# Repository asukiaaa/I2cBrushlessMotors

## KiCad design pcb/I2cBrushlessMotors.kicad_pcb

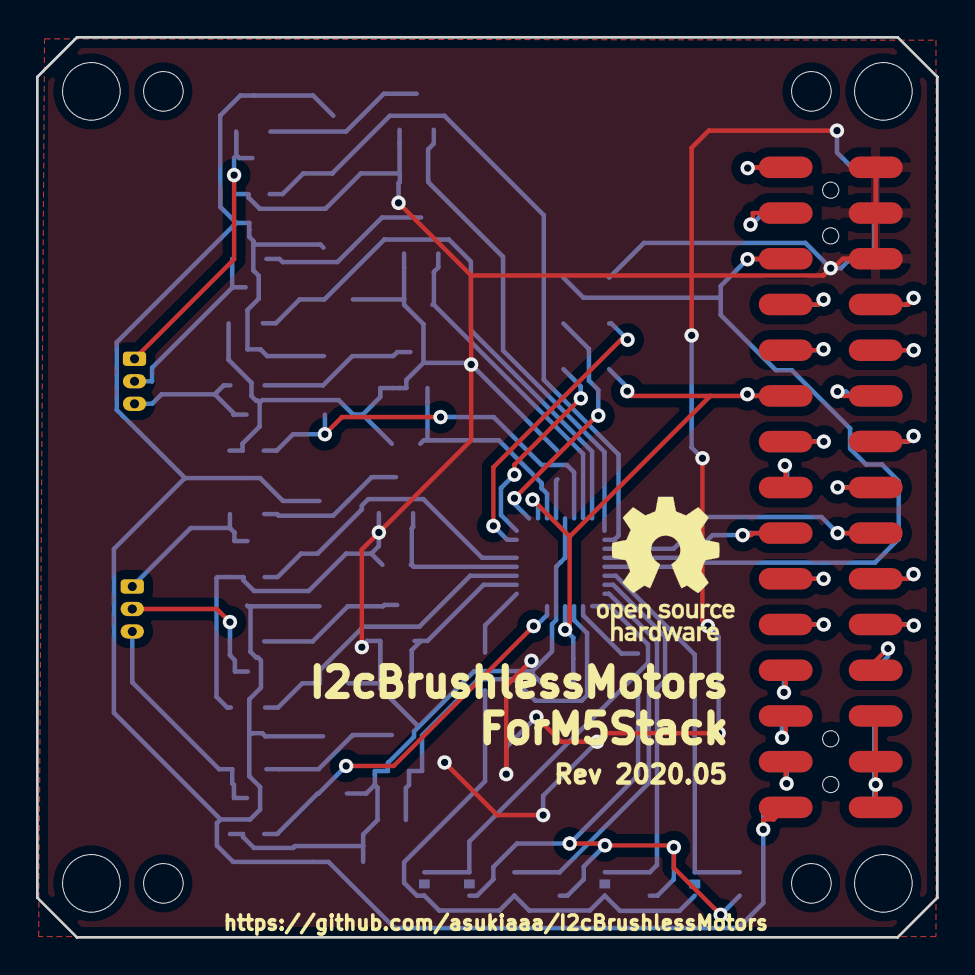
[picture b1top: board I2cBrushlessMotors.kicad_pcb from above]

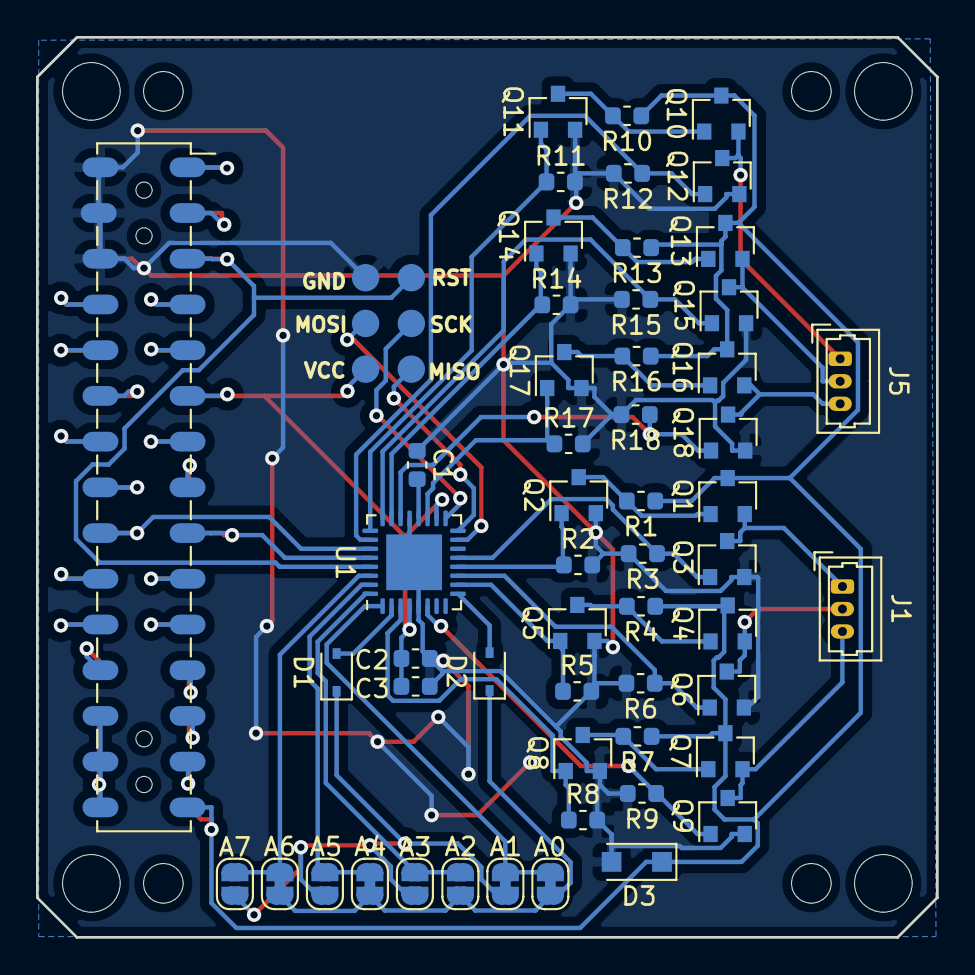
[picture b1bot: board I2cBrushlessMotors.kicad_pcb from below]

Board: 2 copper layers, 50.0 x 50.0 mm, 64 parts (55 on the bottom side), 62 nets.

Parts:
A0, A1, A4, A6: NC; SolderJumper-2_P1.3mm_Bridged_RoundedPad1.0x1.5mm
A2, A3, A5, A7: NO; SolderJumper-2_P1.3mm_Open_RoundedPad1.0x1.5mm
C1, C3: 0.1uf; C_0603_1608Metric
C2: 1uf; C_0603_1608Metric
D1, D2: D; D_SOD-323
D3: D; D_SOD-123F
J1, J5: Conn_01x03; Molex_PicoBlade_53047-0310_1x03_P1.25mm_Vertical
J2: Conn_01x06; 2x03_P2.54mm_Pads
J3: Header; PinHeader_2x15_P2.54mm_M5Stack
J4: Socket; PinSocket_2x15_P2.54mm_Vertical_SMD_just_for_M5Stack_bottom
Q1, Q4, Q7, Q10, Q13, Q16: Q_PMOS_GSD; SOT-23
Q2, Q3, Q5, Q6, Q8, Q9, Q11, Q12, Q14, Q15, Q17, Q18: Q_NMOS_GSD; SOT-23
R1, R2, R3, R4, R5, R6, R7, R8, R9, R10, R11, R12, R13, R14, R15, R16, R17, R18: 10k; R_0603_1608Metric
REF1, REF4, REF6, REF9: MountingHole_3.2mm_M3
REF2, REF3, REF7, REF8: MountingHole_2.2mm_M2
U1: ATmega328PB-MU; QFN-32-1EP_5x5mm_P0.5mm_EP3.1x3.1mm

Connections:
+3V3: C2.2, C3.2, J2.2, J3.11, J4.11, U1.4, U1.18
+5V: J3.27, J4.27
+BATT: D3.1, J3.29, J4.29, Q1.3, Q4.3, Q7.3, Q10.3, Q13.3, Q16.3, R1.1, R4.1, R7.1, R10.1, R13.1, R16.1
/0: J3.23, J4.23
/1: J3.13, J4.13
/2: J3.20, J4.20
/3: J3.14, J4.14
/5: J3.19, J4.19
/12: J3.22, J4.22
/13: J3.21, J4.21
/15: J3.24, J4.24
/16: J3.16, J4.16
/17: J3.15, J4.15
/18: J3.12, J4.12
/19: J3.10, J4.10
/21_SDA: J3.18, J4.18, U1.27
/22_SCL: J3.17, J4.17, U1.28
/23: J3.8, J4.8
/25: J3.7, J4.7
/26: J3.9, J4.9
/34: J3.25, J4.25
/35: J3.1, J4.1
/36: J3.3, J4.3
/A01: A0.1, A1.1, U1.1
/A23: A2.1, A3.1, U1.32
/A45: A4.1, A5.1, U1.31
/A67: A6.1, A7.1, U1.30
/HPWR: J3.26, J3.28, J3.30, J4.26, J4.28, J4.30
/M1A: J1.1, Q1.2, Q3.3
/M1AH: Q2.1, R2.1, U1.12
/M1AL: Q3.1, R3.1, U1.13
/M1B: J1.2, Q4.2, Q6.3
/M1BH: Q5.1, R5.1, U1.10
/M1BL: Q6.1, R6.1, U1.11
/M1C: J1.3, Q7.2, Q9.3
/M1CH: Q8.1, R8.1, U1.3
/M1CL: Q9.1, R9.1, U1.6
/M2A: J5.1, Q10.2, Q12.3
/M2AH: Q11.1, R11.1, U1.25
/M2AL: Q12.1, R12.1, U1.26
/M2B: J5.2, Q13.2, Q15.3
/M2BH: Q14.1, R14.1, U1.23
/M2BL: Q15.1, R15.1, U1.24
/M2C: J5.3, Q16.2, Q18.3
/M2CH: Q17.1, R17.1, U1.19
/M2CL: Q18.1, R18.1, U1.22
/MISO: J2.1, U1.16
/MOSI: J2.4, U1.15
/RST: J2.5, J3.5, J4.5, U1.29
/SCK: J2.3, U1.17
GND: C1.1, C2.1, C3.1, D3.2, J2.6, J3.2, J3.4, J3.6, J4.2, J4.4, J4.6, Q2.2, Q3.2, Q5.2, Q6.2, Q8.2, Q9.2, Q11.2, Q12.2, Q14.2, Q15.2, Q17.2, Q18.2, R2.2, R3.2, R5.2, R6.2, R8.2, R9.2, R11.2, R12.2, R14.2, R15.2, R17.2, R18.2, U1.5, U1.21, U1.33
unnamed: A0.2, A2.2, A4.2, A6.2, D2.1
unnamed: A1.2, A3.2, A5.2, A7.2, D1.1
unnamed: C1.2, U1.20
unnamed: D1.2, U1.2
unnamed: D2.2, U1.9
unnamed: Q1.1, Q2.3, R1.2
unnamed: Q4.1, Q5.3, R4.2
unnamed: Q7.1, Q8.3, R7.2
unnamed: Q10.1, Q11.3, R10.2
unnamed: Q13.1, Q14.3, R13.2
unnamed: Q16.1, Q17.3, R16.2

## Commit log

2020-05-05 Apply vertical connector
